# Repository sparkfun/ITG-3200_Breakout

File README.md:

ITG-3200 Breakout Board
===================================================

[
*Triple-Axis Digital-Output Gyro ITG-3200 Breakout(SEN-11977)*](https://www.sparkfun.com/products/11977)

This is a breakout board for InvenSense's ITG-3200. This sensor is triple-axis, digital output and a MEMS gyroscope.
It runs between 2.1 and 3.6V, and communicates over I2C.

Repository Contents
-------------------
* **/Firmware** - Any firmware that the part ships with, 
* **/Hardware** - All Eagle design files (.brd, .sch, .STL)
* **/Production** - Test bed files and production panel files

License Information
-------------------
The hardware is released under [Creative Commons Share-alike 3.0](http://creativecommons.org/licenses/by-sa/3.0/).  
All other code is open source so please feel free to do anything you want with it; you buy me a beer if you use this and we meet someday ([Beerware license](http://en.wikipedia.org/wiki/Beerware)).

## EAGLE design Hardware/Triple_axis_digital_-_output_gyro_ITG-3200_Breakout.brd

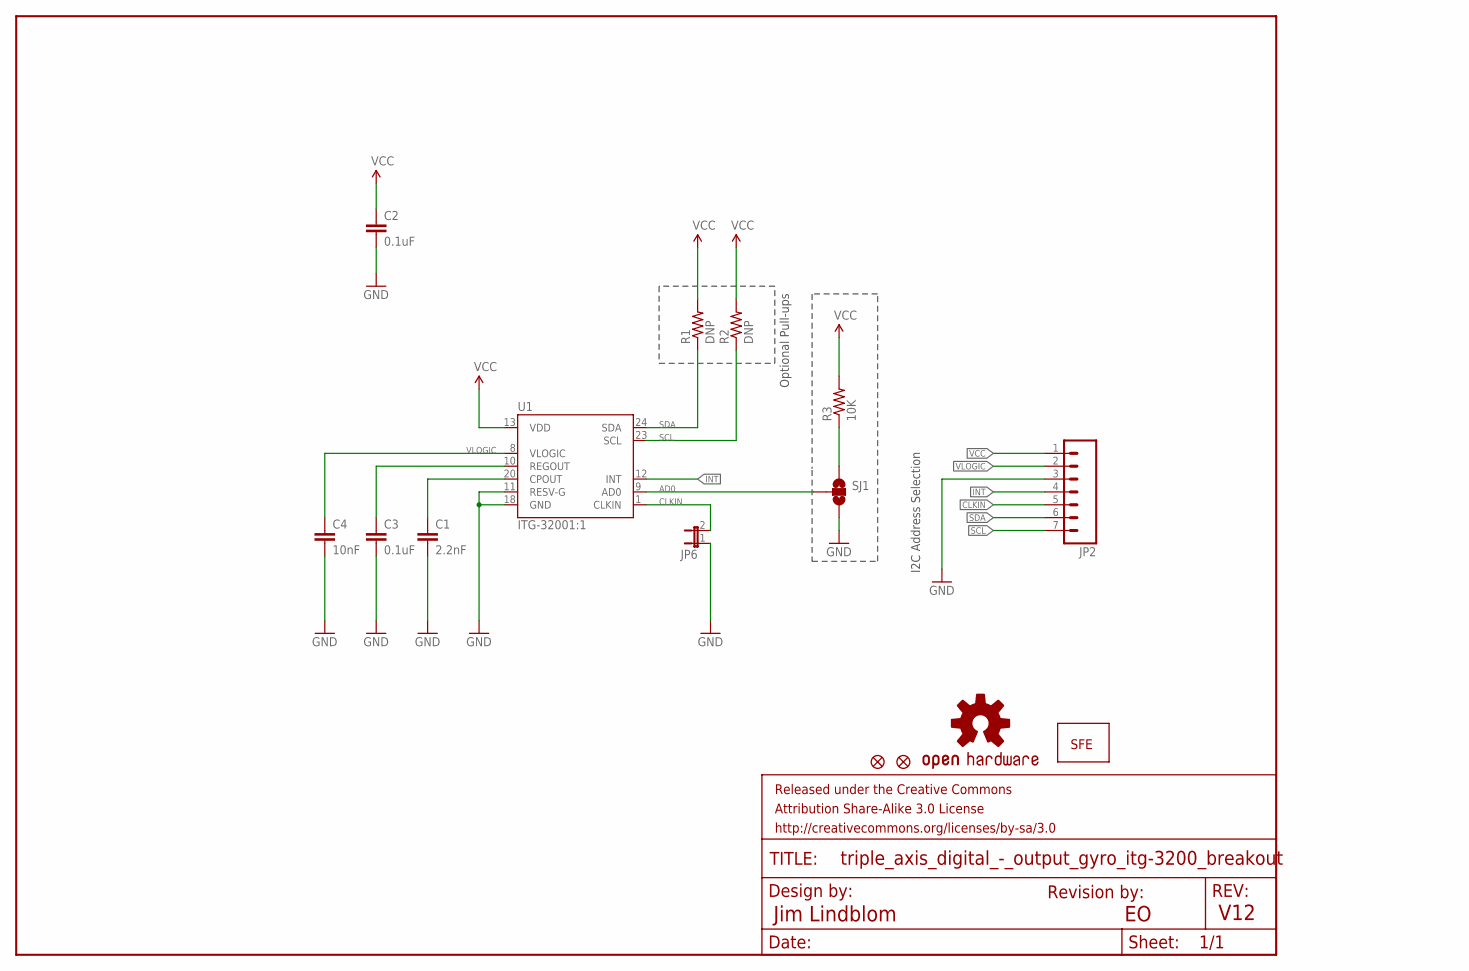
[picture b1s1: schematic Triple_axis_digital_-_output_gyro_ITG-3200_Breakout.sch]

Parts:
C1: 2.2nF; 0603-CAP
C2, C3: 0.1uF; 0603-CAP
C4: 10nF; 0603-CAP
FID1, FID2: FIDUCIALUFIDUCIAL; MICRO-FIDUCIAL
FRAME1: FRAME-LETTER; CREATIVE_COMMONS
JP2: M07; 1X07
JP6: JUMPER-2SMD-NO; SJ_2S-NO
LOGO1: OSHW-LOGOS; OSHW-LOGO-S
LOGO2: LOGO-SFESK; SFE-LOGO-FLAME
R1, R2: DNP; 0603-RES
R3: 10K; 0603-RES
SJ1: SOLDERJUMPER_2WAYPASTE1&2; SJ_3_PASTE1&2
U1: ITG-32001:1; QFN-24_ITG3200_1:1

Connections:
AD0: SJ1.2, U1.9 (AD0)
CLKIN: JP2.5, JP6.2, U1.1 (CLKIN)
GND: C1.2, C2.2, C3.2, C4.2, JP2.3, JP6.1, SJ1.3, U1.11 (RESV-G), U1.18 (GND)
INT: JP2.4, U1.12 (INT)
unnamed: C1.1, U1.20 (CPOUT)
unnamed: C3.1, U1.10 (REGOUT)
unnamed: R3.1, SJ1.1
SCL: JP2.7, R2.1, U1.23 (SCL)
SDA: JP2.6, R1.1, U1.24 (SDA)
VCC: C2.1, JP2.1, R1.2, R2.2, R3.2, U1.13 (VDD)
VLOGIC: C4.1, JP2.2, U1.8 (VLOGIC)

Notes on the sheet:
Optional Pull-ups
I2C Address Selection
Jim Lindblom
V12
Revision by:

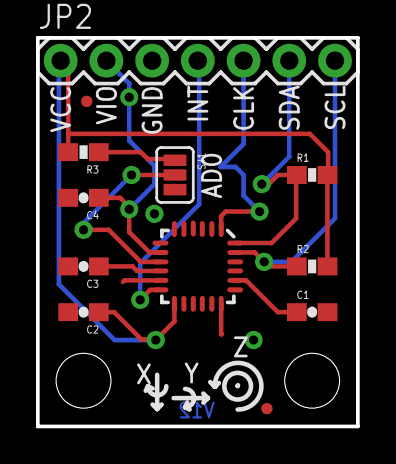
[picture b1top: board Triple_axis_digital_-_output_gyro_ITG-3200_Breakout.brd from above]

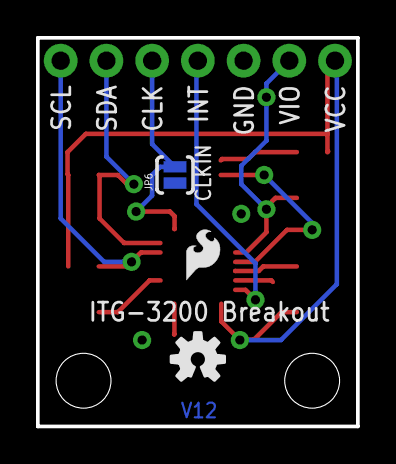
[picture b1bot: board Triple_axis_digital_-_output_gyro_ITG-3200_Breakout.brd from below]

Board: 2 copper layers, 17.8 x 21.6 mm, 18 parts (3 on the bottom side), 11 nets.

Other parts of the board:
U$1, U$2: STAND-OFF-TIGHT

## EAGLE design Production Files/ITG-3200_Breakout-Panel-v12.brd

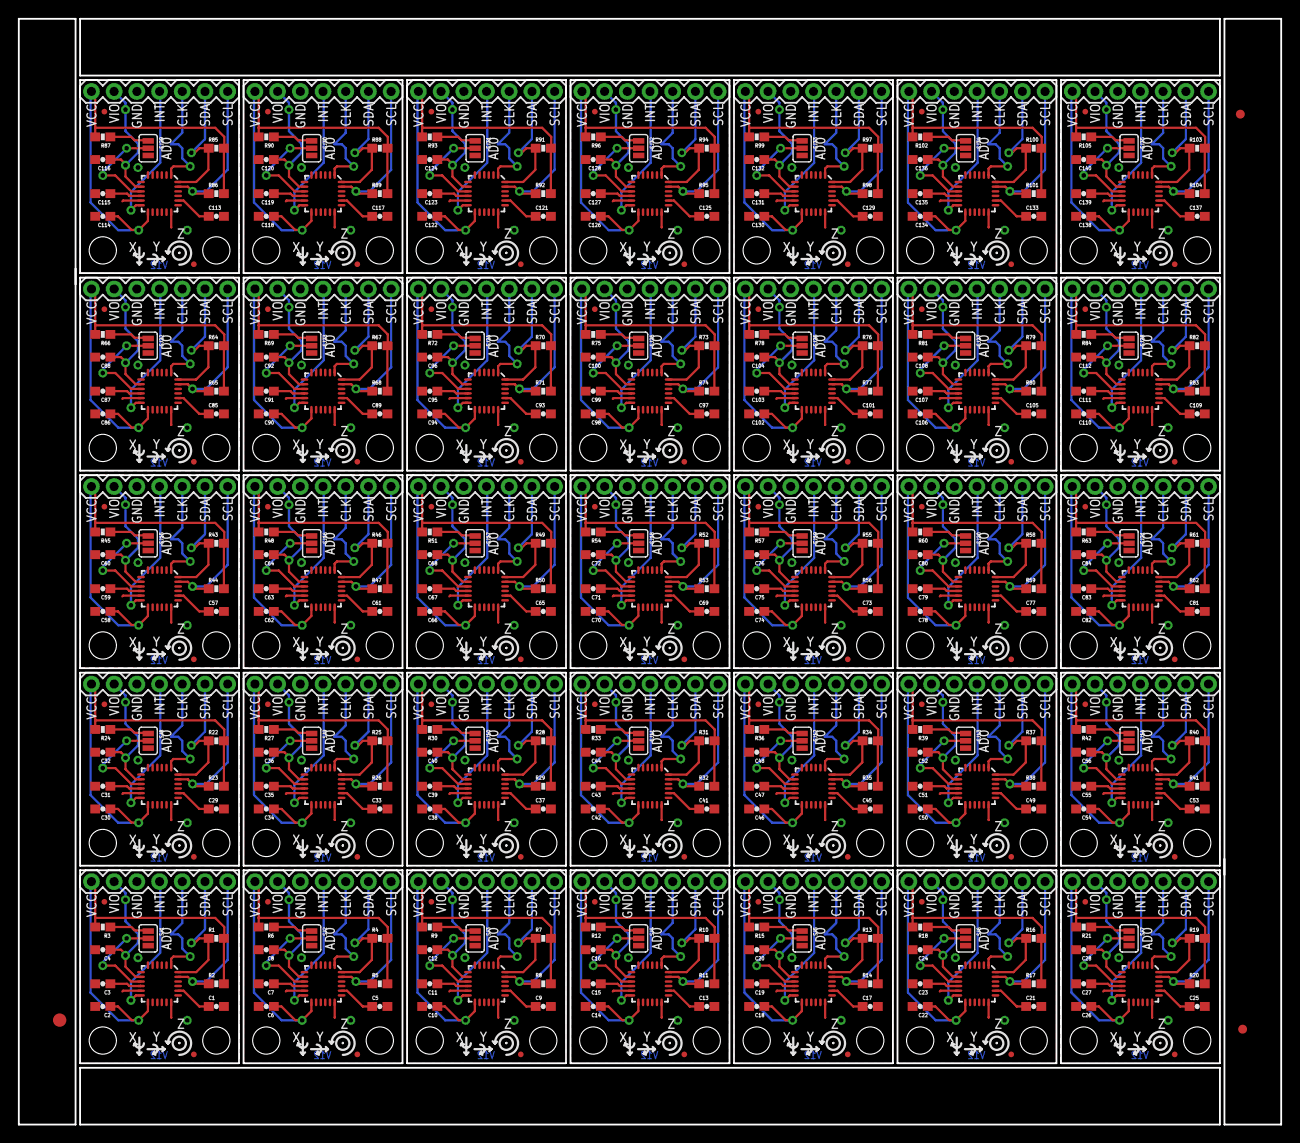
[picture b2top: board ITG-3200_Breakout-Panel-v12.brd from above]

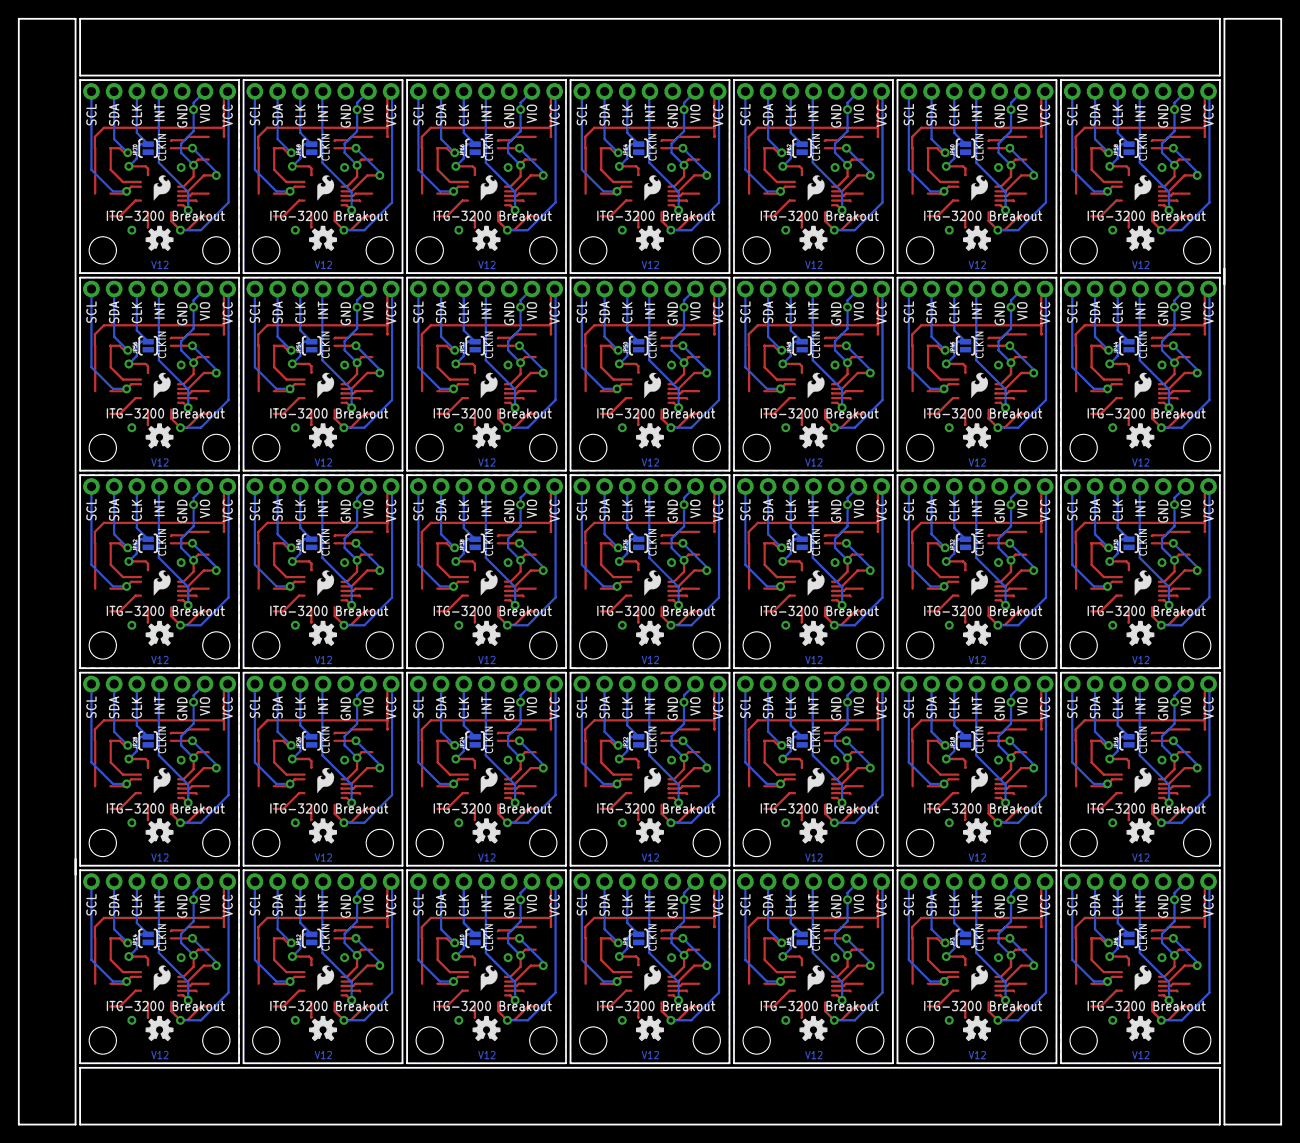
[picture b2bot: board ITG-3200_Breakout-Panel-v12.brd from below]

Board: 2 copper layers, 141.2 x 123.7 mm, 598 parts (105 on the bottom side), 385 nets.

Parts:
C1, C5, C9, C13, C17, C21, C25, C29, C33, C37, C41, C45, C49, C53, C57, C61, C65, C69, C73, C77, C81, C85, C89, C93, C97, C101, C105, C109, C113, C117, C121, C125, C129, C133, C137: 2.2nF; 0603-CAP
C2, C3, C6, C7, C10, C11, C14, C15, C18, C19, C22, C23, C26, C27, C30, C31, C34, C35, C38, C39, C42, C43, C46, C47, C50, C51, C54, C55, C58, C59, C62, C63, C66, C67, C70, C71, C74, C75, C78, C79, C82, C83, C86, C87, C90, C91, C94, C95, C98, C99, C102, C103, C106, C107, C110, C111, C114, C115, C118, C119, C122, C123, C126, C127, C130, C131, C134, C135, C138, C139: 0.1uF; 0603-CAP
C4, C8, C12, C16, C20, C24, C28, C32, C36, C40, C44, C48, C52, C56, C60, C64, C68, C72, C76, C80, C84, C88, C92, C96, C100, C104, C108, C112, C116, C120, C124, C128, C132, C136, C140: 10nF; 0603-CAP
E$1: FIDUCIAL-1.5X3
E$4, E$5: FIDUCIAL-1X2
FID1, FID2, FID3, FID4, FID5, FID6, FID7, FID8, FID9, FID10, FID11, FID12, FID13, FID14, FID15, FID16, FID17, FID18, FID19, FID20, FID21, FID22, FID23, FID24, FID25, FID26, FID27, FID28, FID29, FID30, FID31, FID32, FID33, FID34, FID35, FID36, FID37, FID38, FID39, FID40, FID41, FID42, FID43, FID44, FID45, FID46, FID47, FID48, FID49, FID50, FID51, FID52, FID53, FID54, FID55, FID56, FID57, FID58, FID59, FID60, FID61, FID62, FID63, FID64, FID65, FID66, FID67, FID68, FID69, FID70: FIDUCIALUFIDUCIAL; MICRO-FIDUCIAL
JP1, JP2, JP4, JP7, JP9, JP11, JP13, JP15, JP17, JP19, JP21, JP23, JP25, JP27, JP29, JP31, JP33, JP35, JP37, JP39, JP41, JP43, JP45, JP47, JP49, JP51, JP53, JP55, JP57, JP59, JP61, JP63, JP65, JP67, JP69: 1X07
JP3, JP5, JP6, JP8, JP10, JP12, JP14, JP16, JP18, JP20, JP22, JP24, JP26, JP28, JP30, JP32, JP34, JP36, JP38, JP40, JP42, JP44, JP46, JP48, JP50, JP52, JP54, JP56, JP58, JP60, JP62, JP64, JP66, JP68, JP70: SJ_2S-NO
LOGO1, LOGO3, LOGO5, LOGO7, LOGO9, LOGO11, LOGO13, LOGO15, LOGO17, LOGO19, LOGO21, LOGO23, LOGO25, LOGO27, LOGO29, LOGO31, LOGO33, LOGO35, LOGO37, LOGO39, LOGO41, LOGO43, LOGO45, LOGO47, LOGO49, LOGO51, LOGO53, LOGO55, LOGO57, LOGO59, LOGO61, LOGO63, LOGO65, LOGO67, LOGO69: OSHW-LOGOS; OSHW-LOGO-S
LOGO2, LOGO4, LOGO6, LOGO8, LOGO10, LOGO12, LOGO14, LOGO16, LOGO18, LOGO20, LOGO22, LOGO24, LOGO26, LOGO28, LOGO30, LOGO32, LOGO34, LOGO36, LOGO38, LOGO40, LOGO42, LOGO44, LOGO46, LOGO48, LOGO50, LOGO52, LOGO54, LOGO56, LOGO58, LOGO60, LOGO62, LOGO64, LOGO66, LOGO68, LOGO70: LOGO-SFESK; SFE-LOGO-FLAME
R1, R2, R4, R5, R7, R8, R10, R11, R13, R14, R16, R17, R19, R20, R22, R23, R25, R26, R28, R29, R31, R32, R34, R35, R37, R38, R40, R41, R43, R44, R46, R47, R49, R50, R52, R53, R55, R56, R58, R59, R61, R62, R64, R65, R67, R68, R70, R71, R73, R74, R76, R77, R79, R80, R82, R83, R85, R86, R88, R89, R91, R92, R94, R95, R97, R98, R100, R101, R103, R104: DNP; 0603-RES
R3, R6, R9, R12, R15, R18, R21, R24, R27, R30, R33, R36, R39, R42, R45, R48, R51, R54, R57, R60, R63, R66, R69, R72, R75, R78, R81, R84, R87, R90, R93, R96, R99, R102, R105: 10K; 0603-RES
SJ1, SJ2, SJ3, SJ4, SJ5, SJ6, SJ7, SJ8, SJ9, SJ10, SJ11, SJ12, SJ13, SJ14, SJ15, SJ16, SJ17, SJ18, SJ19, SJ20, SJ21, SJ22, SJ23, SJ24, SJ25, SJ26, SJ27, SJ28, SJ29, SJ30, SJ31, SJ32, SJ33, SJ34, SJ35: SJ_3_PASTE1&2
U1, U2, U3, U4, U5, U6, U7, U8, U9, U10, U11, U12, U13, U14, U15, U16, U17, U18, U19, U20, U21, U22, U23, U24, U25, U26, U27, U28, U29, U30, U31, U32, U33, U34, U35: ITG-32001:1; QFN-24_ITG3200_1:1
U$1, U$2, U$3, U$4, U$5, U$6, U$7, U$8, U$9, U$10, U$11, U$12, U$13, U$14, U$15, U$16, U$17, U$18, U$19, U$20, U$21, U$22, U$23, U$24, U$25, U$26, U$27, U$28, U$29, U$30, U$31, U$32, U$33, U$34, U$35, U$36, U$37, U$38, U$39, U$40, U$41, U$42, U$43, U$44, U$45, U$46, U$47, U$48, U$49, U$50, U$51, U$52, U$53, U$54, U$55, U$56, U$57, U$58, U$59, U$60, U$61, U$62, U$63, U$64, U$65, U$66, U$67, U$68, U$69, U$70: STAND-OFF-TIGHT

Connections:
AD0: SJ1.2, U1.9
AD1: SJ2.2, U2.9
AD2: SJ3.2, U3.9
AD3: SJ4.2, U4.9
AD4: SJ5.2, U5.9
AD5: SJ6.2, U6.9
AD6: SJ7.2, U7.9
AD7: SJ8.2, U8.9
AD8: SJ9.2, U9.9
AD9: SJ10.2, U10.9
AD10: SJ11.2, U11.9
AD11: SJ12.2, U12.9
AD12: SJ13.2, U13.9
AD13: SJ14.2, U14.9
AD14: SJ15.2, U15.9
AD15: SJ16.2, U16.9
AD16: SJ17.2, U17.9
AD17: SJ18.2, U18.9
AD18: SJ19.2, U19.9
AD19: SJ20.2, U20.9
AD20: SJ21.2, U21.9
AD21: SJ22.2, U22.9
AD22: SJ23.2, U23.9
AD23: SJ24.2, U24.9
AD24: SJ25.2, U25.9
AD25: SJ26.2, U26.9
AD26: SJ27.2, U27.9
AD27: SJ28.2, U28.9
AD28: SJ29.2, U29.9
AD29: SJ30.2, U30.9
AD30: SJ31.2, U31.9
AD31: SJ32.2, U32.9
AD32: SJ33.2, U33.9
AD33: SJ34.2, U34.9
AD34: SJ35.2, U35.9
CLKIN: JP2.5, JP6.2, U1.1
CLKIN1: JP1.5, JP3.2, U2.1
CLKIN2: JP4.5, JP5.2, U3.1
CLKIN3: JP7.5, JP8.2, U4.1
CLKIN4: JP9.5, JP10.2, U5.1
CLKIN5: JP11.5, JP12.2, U6.1
CLKIN6: JP13.5, JP14.2, U7.1
CLKIN7: JP15.5, JP16.2, U8.1
CLKIN8: JP17.5, JP18.2, U9.1
CLKIN9: JP19.5, JP20.2, U10.1
CLKIN10: JP21.5, JP22.2, U11.1
CLKIN11: JP23.5, JP24.2, U12.1
CLKIN12: JP25.5, JP26.2, U13.1
CLKIN13: JP27.5, JP28.2, U14.1
CLKIN14: JP29.5, JP30.2, U15.1
CLKIN15: JP31.5, JP32.2, U16.1
CLKIN16: JP33.5, JP34.2, U17.1
CLKIN17: JP35.5, JP36.2, U18.1
CLKIN18: JP37.5, JP38.2, U19.1
CLKIN19: JP39.5, JP40.2, U20.1
CLKIN20: JP41.5, JP42.2, U21.1
CLKIN21: JP43.5, JP44.2, U22.1
CLKIN22: JP45.5, JP46.2, U23.1
CLKIN23: JP47.5, JP48.2, U24.1
CLKIN24: JP49.5, JP50.2, U25.1
CLKIN25: JP51.5, JP52.2, U26.1
CLKIN26: JP53.5, JP54.2, U27.1
CLKIN27: JP55.5, JP56.2, U28.1
CLKIN28: JP57.5, JP58.2, U29.1
CLKIN29: JP59.5, JP60.2, U30.1
CLKIN30: JP61.5, JP62.2, U31.1
CLKIN31: JP63.5, JP64.2, U32.1
CLKIN32: JP65.5, JP66.2, U33.1
CLKIN33: JP67.5, JP68.2, U34.1
CLKIN34: JP69.5, JP70.2, U35.1
GND: C1.2, C2.2, C3.2, C4.2, JP2.3, JP6.1, SJ1.3, U1.11, U1.18
GND1: C5.2, C6.2, C7.2, C8.2, JP1.3, JP3.1, SJ2.3, U2.11, U2.18
GND2: C9.2, C10.2, C11.2, C12.2, JP4.3, JP5.1, SJ3.3, U3.11, U3.18
GND3: C13.2, C14.2, C15.2, C16.2, JP7.3, JP8.1, SJ4.3, U4.11, U4.18
GND4: C17.2, C18.2, C19.2, C20.2, JP9.3, JP10.1, SJ5.3, U5.11, U5.18
GND5: C21.2, C22.2, C23.2, C24.2, JP11.3, JP12.1, SJ6.3, U6.11, U6.18
GND6: C25.2, C26.2, C27.2, C28.2, JP13.3, JP14.1, SJ7.3, U7.11, U7.18
GND7: C29.2, C30.2, C31.2, C32.2, JP15.3, JP16.1, SJ8.3, U8.11, U8.18
GND8: C33.2, C34.2, C35.2, C36.2, JP17.3, JP18.1, SJ9.3, U9.11, U9.18
GND9: C37.2, C38.2, C39.2, C40.2, JP19.3, JP20.1, SJ10.3, U10.11, U10.18
GND10: C41.2, C42.2, C43.2, C44.2, JP21.3, JP22.1, SJ11.3, U11.11, U11.18
GND11: C45.2, C46.2, C47.2, C48.2, JP23.3, JP24.1, SJ12.3, U12.11, U12.18
GND12: C49.2, C50.2, C51.2, C52.2, JP25.3, JP26.1, SJ13.3, U13.11, U13.18
GND13: C53.2, C54.2, C55.2, C56.2, JP27.3, JP28.1, SJ14.3, U14.11, U14.18
GND14: C57.2, C58.2, C59.2, C60.2, JP29.3, JP30.1, SJ15.3, U15.11, U15.18
GND15: C61.2, C62.2, C63.2, C64.2, JP31.3, JP32.1, SJ16.3, U16.11, U16.18
GND16: C65.2, C66.2, C67.2, C68.2, JP33.3, JP34.1, SJ17.3, U17.11, U17.18
GND17: C69.2, C70.2, C71.2, C72.2, JP35.3, JP36.1, SJ18.3, U18.11, U18.18
GND18: C73.2, C74.2, C75.2, C76.2, JP37.3, JP38.1, SJ19.3, U19.11, U19.18
GND19: C77.2, C78.2, C79.2, C80.2, JP39.3, JP40.1, SJ20.3, U20.11, U20.18
GND20: C81.2, C82.2, C83.2, C84.2, JP41.3, JP42.1, SJ21.3, U21.11, U21.18
GND21: C85.2, C86.2, C87.2, C88.2, JP43.3, JP44.1, SJ22.3, U22.11, U22.18
GND22: C89.2, C90.2, C91.2, C92.2, JP45.3, JP46.1, SJ23.3, U23.11, U23.18
GND23: C93.2, C94.2, C95.2, C96.2, JP47.3, JP48.1, SJ24.3, U24.11, U24.18
GND24: C97.2, C98.2, C99.2, C100.2, JP49.3, JP50.1, SJ25.3, U25.11, U25.18
GND25: C101.2, C102.2, C103.2, C104.2, JP51.3, JP52.1, SJ26.3, U26.11, U26.18
GND26: C105.2, C106.2, C107.2, C108.2, JP53.3, JP54.1, SJ27.3, U27.11, U27.18
GND27: C109.2, C110.2, C111.2, C112.2, JP55.3, JP56.1, SJ28.3, U28.11, U28.18
GND28: C113.2, C114.2, C115.2, C116.2, JP57.3, JP58.1, SJ29.3, U29.11, U29.18
GND29: C117.2, C118.2, C119.2, C120.2, JP59.3, JP60.1, SJ30.3, U30.11, U30.18
GND30: C121.2, C122.2, C123.2, C124.2, JP61.3, JP62.1, SJ31.3, U31.11, U31.18
GND31: C125.2, C126.2, C127.2, C128.2, JP63.3, JP64.1, SJ32.3, U32.11, U32.18
GND32: C129.2, C130.2, C131.2, C132.2, JP65.3, JP66.1, SJ33.3, U33.11, U33.18
GND33: C133.2, C134.2, C135.2, C136.2, JP67.3, JP68.1, SJ34.3, U34.11, U34.18
GND34: C137.2, C138.2, C139.2, C140.2, JP69.3, JP70.1, SJ35.3, U35.11, U35.18
INT: JP2.4, U1.12
INT1: JP1.4, U2.12
INT2: JP4.4, U3.12
INT3: JP7.4, U4.12
INT4: JP9.4, U5.12
INT5: JP11.4, U6.12
INT6: JP13.4, U7.12
INT7: JP15.4, U8.12
INT8: JP17.4, U9.12
INT9: JP19.4, U10.12
INT10: JP21.4, U11.12
INT11: JP23.4, U12.12
INT12: JP25.4, U13.12
INT13: JP27.4, U14.12
INT14: JP29.4, U15.12
INT15: JP31.4, U16.12
INT16: JP33.4, U17.12
INT17: JP35.4, U18.12
INT18: JP37.4, U19.12
INT19: JP39.4, U20.12
INT20: JP41.4, U21.12
INT21: JP43.4, U22.12
INT22: JP45.4, U23.12
INT23: JP47.4, U24.12
INT24: JP49.4, U25.12
INT25: JP51.4, U26.12
INT26: JP53.4, U27.12
INT27: JP55.4, U28.12
INT28: JP57.4, U29.12
INT29: JP59.4, U30.12
INT30: JP61.4, U31.12
INT31: JP63.4, U32.12
INT32: JP65.4, U33.12
INT33: JP67.4, U34.12
INT34: JP69.4, U35.12
unnamed: C1.1, U1.20
unnamed: C3.1, U1.10
unnamed: R3.1, SJ1.1
unnamed: C7.1, U2.10
unnamed: C5.1, U2.20
unnamed: R6.1, SJ2.1
unnamed: C11.1, U3.10
unnamed: C9.1, U3.20
unnamed: R9.1, SJ3.1
unnamed: C15.1, U4.10
unnamed: C13.1, U4.20
unnamed: R12.1, SJ4.1
unnamed: C19.1, U5.10
unnamed: C17.1, U5.20
unnamed: R15.1, SJ5.1
unnamed: C23.1, U6.10
unnamed: C21.1, U6.20
unnamed: R18.1, SJ6.1
unnamed: C27.1, U7.10
unnamed: C25.1, U7.20
unnamed: R21.1, SJ7.1
unnamed: C31.1, U8.10
unnamed: C29.1, U8.20
unnamed: R24.1, SJ8.1
unnamed: C35.1, U9.10
unnamed: C33.1, U9.20
unnamed: R27.1, SJ9.1
unnamed: C39.1, U10.10
unnamed: C37.1, U10.20
unnamed: R30.1, SJ10.1
unnamed: C43.1, U11.10
unnamed: C41.1, U11.20
unnamed: R33.1, SJ11.1
unnamed: C47.1, U12.10
unnamed: C45.1, U12.20
unnamed: R36.1, SJ12.1
unnamed: C51.1, U13.10
unnamed: C49.1, U13.20
unnamed: R39.1, SJ13.1
unnamed: C55.1, U14.10
unnamed: C53.1, U14.20
unnamed: R42.1, SJ14.1
unnamed: C59.1, U15.10
unnamed: C57.1, U15.20
unnamed: R45.1, SJ15.1
unnamed: C63.1, U16.10
unnamed: C61.1, U16.20
unnamed: R48.1, SJ16.1
unnamed: C67.1, U17.10
unnamed: C65.1, U17.20
unnamed: R51.1, SJ17.1
unnamed: C71.1, U18.10
unnamed: C69.1, U18.20
unnamed: R54.1, SJ18.1
unnamed: C75.1, U19.10
unnamed: C73.1, U19.20
unnamed: R57.1, SJ19.1
unnamed: C79.1, U20.10
unnamed: C77.1, U20.20
unnamed: R60.1, SJ20.1
unnamed: C83.1, U21.10
unnamed: C81.1, U21.20
unnamed: R63.1, SJ21.1
unnamed: C87.1, U22.10
unnamed: C85.1, U22.20
unnamed: R66.1, SJ22.1
unnamed: C91.1, U23.10
unnamed: C89.1, U23.20
unnamed: R69.1, SJ23.1
unnamed: C95.1, U24.10
unnamed: C93.1, U24.20
unnamed: R72.1, SJ24.1
unnamed: C99.1, U25.10
unnamed: C97.1, U25.20
unnamed: R75.1, SJ25.1
unnamed: C103.1, U26.10
unnamed: C101.1, U26.20
unnamed: R78.1, SJ26.1
unnamed: C107.1, U27.10
unnamed: C105.1, U27.20
unnamed: R81.1, SJ27.1
unnamed: C111.1, U28.10
unnamed: C109.1, U28.20
unnamed: R84.1, SJ28.1
unnamed: C115.1, U29.10
unnamed: C113.1, U29.20
unnamed: R87.1, SJ29.1
unnamed: C119.1, U30.10
unnamed: C117.1, U30.20
unnamed: R90.1, SJ30.1
unnamed: C123.1, U31.10
unnamed: C121.1, U31.20
unnamed: R93.1, SJ31.1
unnamed: C127.1, U32.10
unnamed: C125.1, U32.20
unnamed: R96.1, SJ32.1
unnamed: C131.1, U33.10
unnamed: C129.1, U33.20
unnamed: R99.1, SJ33.1
unnamed: C135.1, U34.10
unnamed: C133.1, U34.20
unnamed: R102.1, SJ34.1
unnamed: C139.1, U35.10
unnamed: C137.1, U35.20
unnamed: R105.1, SJ35.1
SCL: JP2.7, R2.1, U1.23
SCL1: JP1.7, R5.1, U2.23
SCL2: JP4.7, R8.1, U3.23
SCL3: JP7.7, R11.1, U4.23
SCL4: JP9.7, R14.1, U5.23
SCL5: JP11.7, R17.1, U6.23
SCL6: JP13.7, R20.1, U7.23
SCL7: JP15.7, R23.1, U8.23
SCL8: JP17.7, R26.1, U9.23
SCL9: JP19.7, R29.1, U10.23
SCL10: JP21.7, R32.1, U11.23
SCL11: JP23.7, R35.1, U12.23
SCL12: JP25.7, R38.1, U13.23
SCL13: JP27.7, R41.1, U14.23
SCL14: JP29.7, R44.1, U15.23
SCL15: JP31.7, R47.1, U16.23
SCL16: JP33.7, R50.1, U17.23
SCL17: JP35.7, R53.1, U18.23
SCL18: JP37.7, R56.1, U19.23
SCL19: JP39.7, R59.1, U20.23
SCL20: JP41.7, R62.1, U21.23
SCL21: JP43.7, R65.1, U22.23
SCL22: JP45.7, R68.1, U23.23
SCL23: JP47.7, R71.1, U24.23
SCL24: JP49.7, R74.1, U25.23
SCL25: JP51.7, R77.1, U26.23
SCL26: JP53.7, R80.1, U27.23
SCL27: JP55.7, R83.1, U28.23
SCL28: JP57.7, R86.1, U29.23
SCL29: JP59.7, R89.1, U30.23
SCL30: JP61.7, R92.1, U31.23
SCL31: JP63.7, R95.1, U32.23
SCL32: JP65.7, R98.1, U33.23
SCL33: JP67.7, R101.1, U34.23
SCL34: JP69.7, R104.1, U35.23
SDA: JP2.6, R1.1, U1.24
SDA1: JP1.6, R4.1, U2.24
SDA2: JP4.6, R7.1, U3.24
SDA3: JP7.6, R10.1, U4.24
SDA4: JP9.6, R13.1, U5.24
SDA5: JP11.6, R16.1, U6.24
SDA6: JP13.6, R19.1, U7.24
SDA7: JP15.6, R22.1, U8.24
SDA8: JP17.6, R25.1, U9.24
SDA9: JP19.6, R28.1, U10.24
SDA10: JP21.6, R31.1, U11.24
SDA11: JP23.6, R34.1, U12.24
SDA12: JP25.6, R37.1, U13.24
SDA13: JP27.6, R40.1, U14.24
SDA14: JP29.6, R43.1, U15.24
SDA15: JP31.6, R46.1, U16.24
SDA16: JP33.6, R49.1, U17.24
SDA17: JP35.6, R52.1, U18.24
SDA18: JP37.6, R55.1, U19.24
SDA19: JP39.6, R58.1, U20.24
SDA20: JP41.6, R61.1, U21.24
SDA21: JP43.6, R64.1, U22.24
SDA22: JP45.6, R67.1, U23.24
SDA23: JP47.6, R70.1, U24.24
SDA24: JP49.6, R73.1, U25.24
SDA25: JP51.6, R76.1, U26.24
SDA26: JP53.6, R79.1, U27.24
SDA27: JP55.6, R82.1, U28.24
SDA28: JP57.6, R85.1, U29.24
SDA29: JP59.6, R88.1, U30.24
SDA30: JP61.6, R91.1, U31.24
SDA31: JP63.6, R94.1, U32.24
SDA32: JP65.6, R97.1, U33.24
SDA33: JP67.6, R100.1, U34.24
SDA34: JP69.6, R103.1, U35.24
VCC: C2.1, JP2.1, R1.2, R2.2, R3.2, U1.13
VCC1: C6.1, JP1.1, R4.2, R5.2, R6.2, U2.13
VCC2: C10.1, JP4.1, R7.2, R8.2, R9.2, U3.13
VCC3: C14.1, JP7.1, R10.2, R11.2, R12.2, U4.13
VCC4: C18.1, JP9.1, R13.2, R14.2, R15.2, U5.13
VCC5: C22.1, JP11.1, R16.2, R17.2, R18.2, U6.13
VCC6: C26.1, JP13.1, R19.2, R20.2, R21.2, U7.13
VCC7: C30.1, JP15.1, R22.2, R23.2, R24.2, U8.13
VCC8: C34.1, JP17.1, R25.2, R26.2, R27.2, U9.13
VCC9: C38.1, JP19.1, R28.2, R29.2, R30.2, U10.13
VCC10: C42.1, JP21.1, R31.2, R32.2, R33.2, U11.13
VCC11: C46.1, JP23.1, R34.2, R35.2, R36.2, U12.13
VCC12: C50.1, JP25.1, R37.2, R38.2, R39.2, U13.13
VCC13: C54.1, JP27.1, R40.2, R41.2, R42.2, U14.13
VCC14: C58.1, JP29.1, R43.2, R44.2, R45.2, U15.13
VCC15: C62.1, JP31.1, R46.2, R47.2, R48.2, U16.13
VCC16: C66.1, JP33.1, R49.2, R50.2, R51.2, U17.13
VCC17: C70.1, JP35.1, R52.2, R53.2, R54.2, U18.13
VCC18: C74.1, JP37.1, R55.2, R56.2, R57.2, U19.13
VCC19: C78.1, JP39.1, R58.2, R59.2, R60.2, U20.13
VCC20: C82.1, JP41.1, R61.2, R62.2, R63.2, U21.13
VCC21: C86.1, JP43.1, R64.2, R65.2, R66.2, U22.13
VCC22: C90.1, JP45.1, R67.2, R68.2, R69.2, U23.13
VCC23: C94.1, JP47.1, R70.2, R71.2, R72.2, U24.13
VCC24: C98.1, JP49.1, R73.2, R74.2, R75.2, U25.13
VCC25: C102.1, JP51.1, R76.2, R77.2, R78.2, U26.13
VCC26: C106.1, JP53.1, R79.2, R80.2, R81.2, U27.13
VCC27: C110.1, JP55.1, R82.2, R83.2, R84.2, U28.13
VCC28: C114.1, JP57.1, R85.2, R86.2, R87.2, U29.13
VCC29: C118.1, JP59.1, R88.2, R89.2, R90.2, U30.13
VCC30: C122.1, JP61.1, R91.2, R92.2, R93.2, U31.13
VCC31: C126.1, JP63.1, R94.2, R95.2, R96.2, U32.13
VCC32: C130.1, JP65.1, R97.2, R98.2, R99.2, U33.13
VCC33: C134.1, JP67.1, R100.2, R101.2, R102.2, U34.13
VCC34: C138.1, JP69.1, R103.2, R104.2, R105.2, U35.13
VLOGIC: C4.1, JP2.2, U1.8
VLOGIC1: C8.1, JP1.2, U2.8
VLOGIC2: C12.1, JP4.2, U3.8
VLOGIC3: C16.1, JP7.2, U4.8
VLOGIC4: C20.1, JP9.2, U5.8
VLOGIC5: C24.1, JP11.2, U6.8
VLOGIC6: C28.1, JP13.2, U7.8
VLOGIC7: C32.1, JP15.2, U8.8
VLOGIC8: C36.1, JP17.2, U9.8
VLOGIC9: C40.1, JP19.2, U10.8
VLOGIC10: C44.1, JP21.2, U11.8
VLOGIC11: C48.1, JP23.2, U12.8
VLOGIC12: C52.1, JP25.2, U13.8
VLOGIC13: C56.1, JP27.2, U14.8
VLOGIC14: C60.1, JP29.2, U15.8
VLOGIC15: C64.1, JP31.2, U16.8
VLOGIC16: C68.1, JP33.2, U17.8
VLOGIC17: C72.1, JP35.2, U18.8
VLOGIC18: C76.1, JP37.2, U19.8
VLOGIC19: C80.1, JP39.2, U20.8
VLOGIC20: C84.1, JP41.2, U21.8
VLOGIC21: C88.1, JP43.2, U22.8
VLOGIC22: C92.1, JP45.2, U23.8
VLOGIC23: C96.1, JP47.2, U24.8
VLOGIC24: C100.1, JP49.2, U25.8
VLOGIC25: C104.1, JP51.2, U26.8
VLOGIC26: C108.1, JP53.2, U27.8
VLOGIC27: C112.1, JP55.2, U28.8
VLOGIC28: C116.1, JP57.2, U29.8
VLOGIC29: C120.1, JP59.2, U30.8
VLOGIC30: C124.1, JP61.2, U31.8
VLOGIC31: C128.1, JP63.2, U32.8
VLOGIC32: C132.1, JP65.2, U33.8
VLOGIC33: C136.1, JP67.2, U34.8
VLOGIC34: C140.1, JP69.2, U35.8

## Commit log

2013-07-03 BRD, SCH, V11, gitignore, from network
2013-07-10 V12 revision, see details
    -added new 1:1 ITG-3200 FP
    -routed all traces directly out from IC landings
    -added standoff holes to board
    -added OSHW and SFE flame
    -changed version to 12
2013-07-10 fixed z axis silk to incorporate circle and a dot
2013-07-12 Changed a few trace routes
2013-07-12 deleted old files that were named incorrectly
2013-07-12 re-routed traces to enter pads at a 90
2013-07-15 Post Eng. Review fixes
    -Moved axis symbols to be centered with the IC
    -Added pull-up res. for ADO line/jumper
    -Labeled bottom jumper
2013-07-16 added GND symbol on header in schematic instead of flag.
2013-09-11 Panel Created
2013-10-16 Added Firmware folder with Arduino Sketch
2013-10-31 Updating README with product information
2015-02-03 Adding simple sketch to repo
2019-11-06 Fixing incorrect use of Wire.beginTransmission
    Fixing incorrect use of Wire.beginTransmission
2019-11-06 Fixing incorrect usage of beginTransmission and endTransmission
    Fixing incorrect usage of beginTransmission and endTransmission
2025-06-27 Update README.md
    Updating link

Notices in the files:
parts and their libraries:
SparkFun-DigitalIC: Licensing: CC v3.0 Share-Alike You are welcome to use this library for commercial purposes.
SparkFun-Aesthetics: Released under the Creative Commons Attribution Share-Alike 3.0 License
SparkFun-Aesthetics: Released under the Creative Commons
